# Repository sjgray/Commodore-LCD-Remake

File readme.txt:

CLCD Re-Make Project  by Steve Gray		cbmsteve.ca
====================  and Mike Naberezny        mikenaberezny.com

The goal of this project is to remake/recreate the never released
Commodore LCD computer. Only a few working prototypes were ever
made. These were almost production ready and luckily a few survived
and information about them was released. Thanks go to Jeff Porter
and Bil Herd for helping with this project. Since the LCD computer
was never produced there are no spare parts and no way to replace
them. Several things are no longer available, such as the custom
chips, keyboard, case and LCD Panel, so we must recreate them or
adapt the design to use modern replacements and similar available parts.

Please see the webpage for more info: http://www.cbmsteve.ca/clcd/index.html

*** This is a work in progress!!! The project is currently incomplete.
    Files are provided for information only. Do not attempt to build
    it unless you are willing to debug and fix things. I will not be
    able to support you. As this is a personal project I can not say
    if or when this might be fully functional!

*** GERBER files have not been provided. They may be made available when
    the project is in a more stable/working state.

DESIGN
======

Schematics
----------

Bil Herd had saved all 4 original pages of the CLCD schematics however
one was misplaced. The 3 pages were sent to Mike, scanned in high-res,
and returned to Bil. Later Bil eventually found the missing page and took
several photos. I (Steve) stitched them together into one photo and used
it as a guide for recreating the missing page.

Design Changes
--------------

Since the custom chips and other parts of the computer were not available
I decided to use a CPLD for the MMU/glue and the C128's VDC chip for the
video. A 32K Dual-port RAM was used for the main memory. Both the CPU and
VDC can access this memory independently/simultaneously and the CPU can
write to it directly without the need to go through the VDC registers. This
means writing to the (text) screen works like the original machine. Only
a small patch is needed for the KERNAL.

Western Design Center still makes 6502-series chips and these were used in
the new design. The original 65C102 CPU was replaced with a 65C02 which is
fully compatible. Similarly equivalent WDC IO chips were also available but
in a smaller PLCC package.

Everything is powered by a simple 12V supply.

LCD Panel/Video
---------------

The original 80x16 (480x128 pixel) monochrome LCD panel was replaced by a
modern widescreen colour panel of roughly the same size. It includes a
controller board with HDMI and composite video inputs. We will use the HDMI
input for best quality. The VDC's RGBI output will be converted to HDMI
using an RGB2HDMI converter. There is an RGBI output connector for an
external display.

Keyboard
--------

Two keyboards were designed with MX switches. One design is like the
original keyboard and uses the diamond arrow cursor. The other design uses
an inverted-T cursor. This design was chosen so that normal keycaps
could be used. Included are files to create custom printed keycaps from
maxkeyboard.com. Custom 3D printed keycaps that match the original, including
the diamond cursor, are in progress for the next revision.

EPROM-PLA
---------

The V1 board initially required the EPROM-PLA board, which plugged into the
expansion connector. This board used an EPROM to emulate a PLA that did
decoding for basic functionality. It is no longer required as it has been
replaced by Mike's CPLD implementation.

Case
----

I have designed a case that can be 3D printed. I used Light-beige PLA.
It must be assembled from multiple pieces and requires brass screw inserts
to hold it together. The initial case is an approximation and has been
designed to accommodate the new LCD panel and it's controller and the
RGB2HDMI adapter. All ports are on the back.

Missing Features
----------------

The battery/power, modem, and barcode port features were not implemented in
the initial design but can hopefully be added later as the design progresses.

V1 PROTO
========

V1 is the first prototype that was developed and demonstrated to Jeff Porter
and Bil Herd.

The first prototype PCB was produced but it requires multiple fixes to
correct errors. These were done by Mike. Mike also did further disassembly of
the CLCD KERNAL to be able to re-assemble it back to an original binary and
then patch it to get the VDC working. He also added serial IO for debug purposes.
Mike wrote the CPLD code that functions like a programmed logic array (PLA) to
map in the 32K RAM, KERNAL ROM and IO. The machine is able to boot.

The MMU has not been implemented yet, so the machine can only boot to the
machine-language monitor at this time. The first prototype PCB was a
proof-of-concept and the ports and placement were not designed to match
the original PCB.

I designed a 3D printed case based on existing prototype photos and some original
documentation, but without any complete measurements. It is split into multiple
pieces for easier printing. It is able to open like the original and uses the
inverted-T keyboard version, colour LCD panel with controller and RGB2HDMI adapter.
All ports are along the back of the computer, and the battery compartment allows
access to the RGB2HDMI adapter's buttons.

When Mike visited Jeff he was able to take detailed photographs and measurements
which will be used for the next version. 

V2 PROTO
========

A V2 design is in the works to correct the errors in the V1 Proto PCB.
Additional work is required for the CPLD to add the MMU functionality that
will allow the machine to run the application ROMS, including the normal
menu system.

As of the initial GitHub commit some fixes have been made but there is more
to do. Routing and parts placement is not complete.

A better keyboard will be designed that will support the low-profile MX
switches and use the replica 3D-designed keycaps.

Future Goals
------------

These are just ideas for future goals.

- Better PCB layout to more match the original pcb
- Better keyboard - Low Profile switches and replica keycaps
- Better case
- MMU support for ROM banking and menu system
- Smaller RGBI to HDMI adapter (current is very tight fit)
- Support for graphics mode.
- Modem support? Perhaps a WIFI solution?
- Internal IEC drive?
- Battery power
- Recreation of custom chips.. not easy
- Disassembly of other built-in apps
- Add support for colour or more screen sizes (40x25, 80x25 etc)
- Replica disk drive (1581 case) and printer (Epson P-80)

Additional Info
---------------

My Facebook group............: https://www.facebook.com/groups/806261867281489
Mike's firmware disassembly..: https://github.com/mnaberez/clcd
Mike's firmware and info page: https://mikenaberezny.com/2008/10/04/commodore-lcd-firmware/
Jeff Porter's LCD prototype..: https://flickr.com/photos/mnaberez/albums/72177720308500331/
Jeff Porter's LCD printer....: https://flickr.com/photos/mnaberez/albums/72177720308512645/
Commodore LCD Emulator Online: http://commodore-lcd.lgb.hu/emulator.html
MAME (Has CLCD emulation)....: https://www.mamedev.org/

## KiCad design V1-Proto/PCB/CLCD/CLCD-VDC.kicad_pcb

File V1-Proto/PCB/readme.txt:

CLCD Re-Make Project by Steve Gray and Mike Naberezny
==================== CBMSTEVE.CA

This folder contains:

CLCD      - Kicad design files for CLCD Proto V1 which does not work without fixes
KEYBOARD  - Kicad design files for CLCD Keyboard with Inverted-T cursor. Requires one fix
PLA-BOARD - Kicad design files for EPROM PLA Board - no longer required
_FIXES    - Pictures of fixes required to make the V1 Prototype CLCD board functional

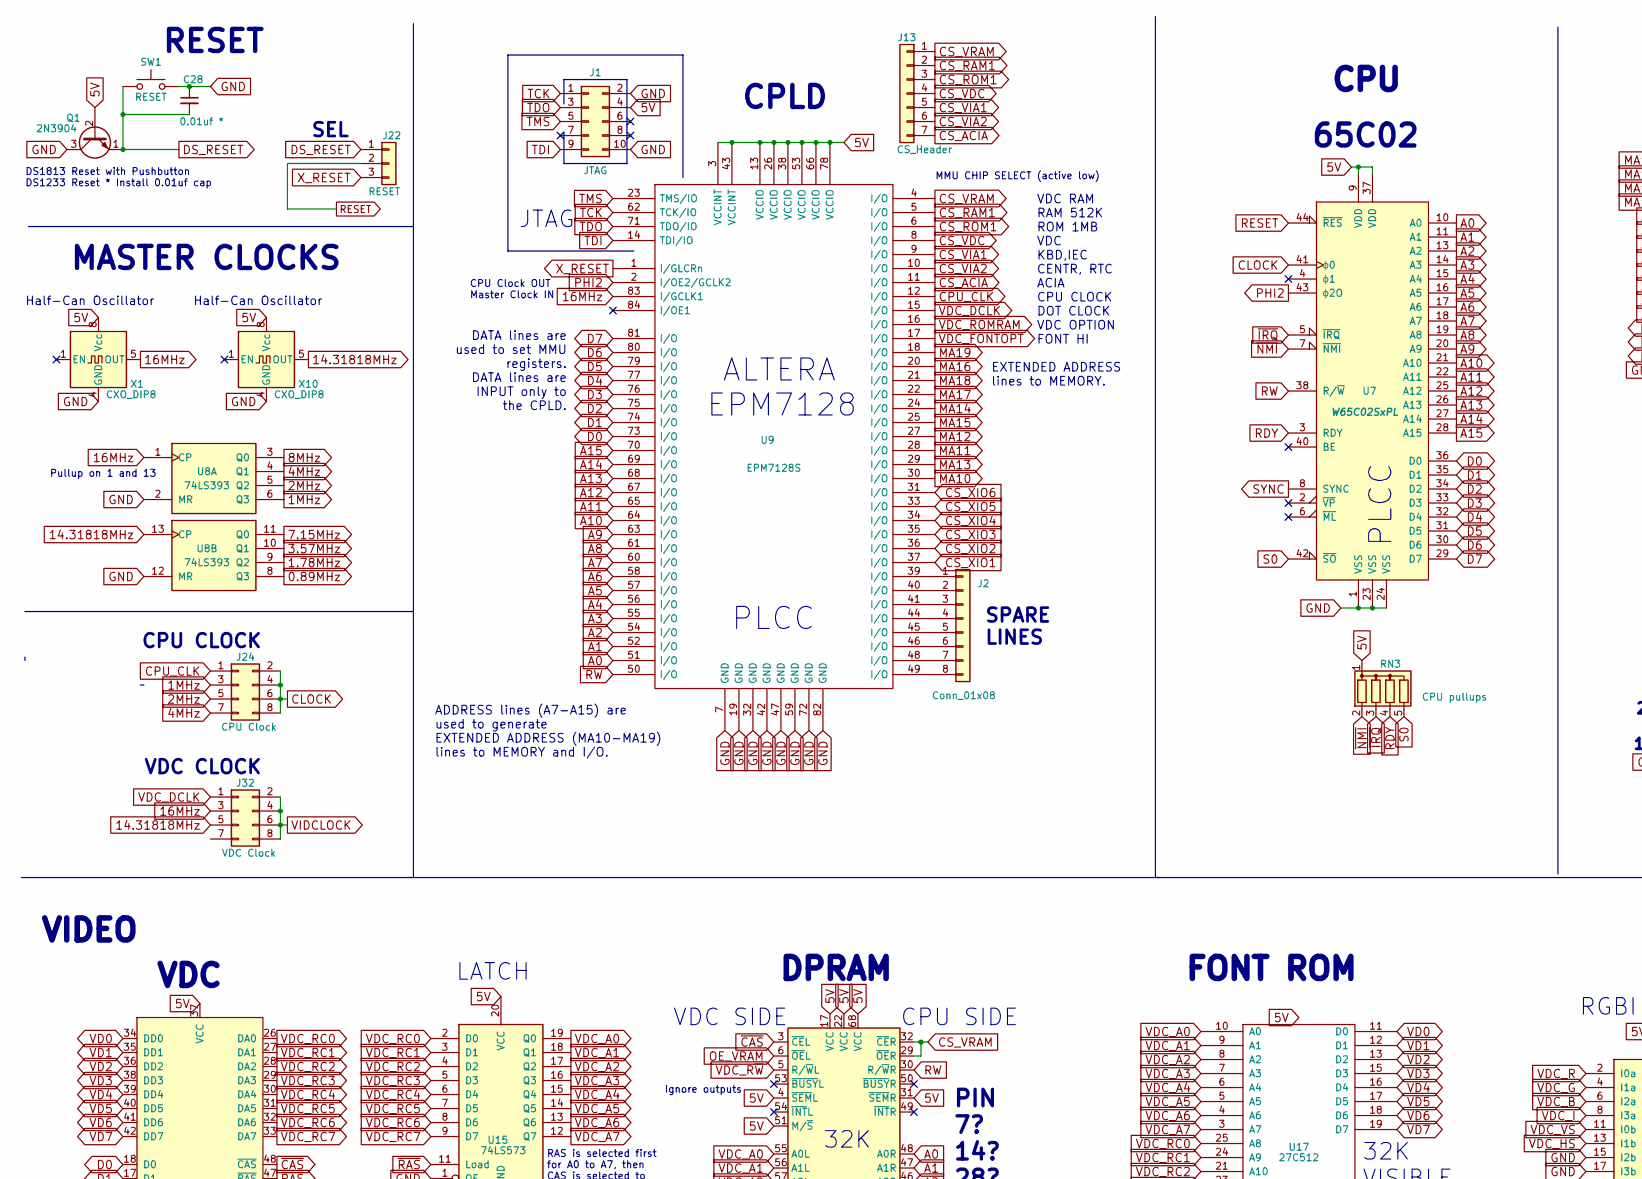
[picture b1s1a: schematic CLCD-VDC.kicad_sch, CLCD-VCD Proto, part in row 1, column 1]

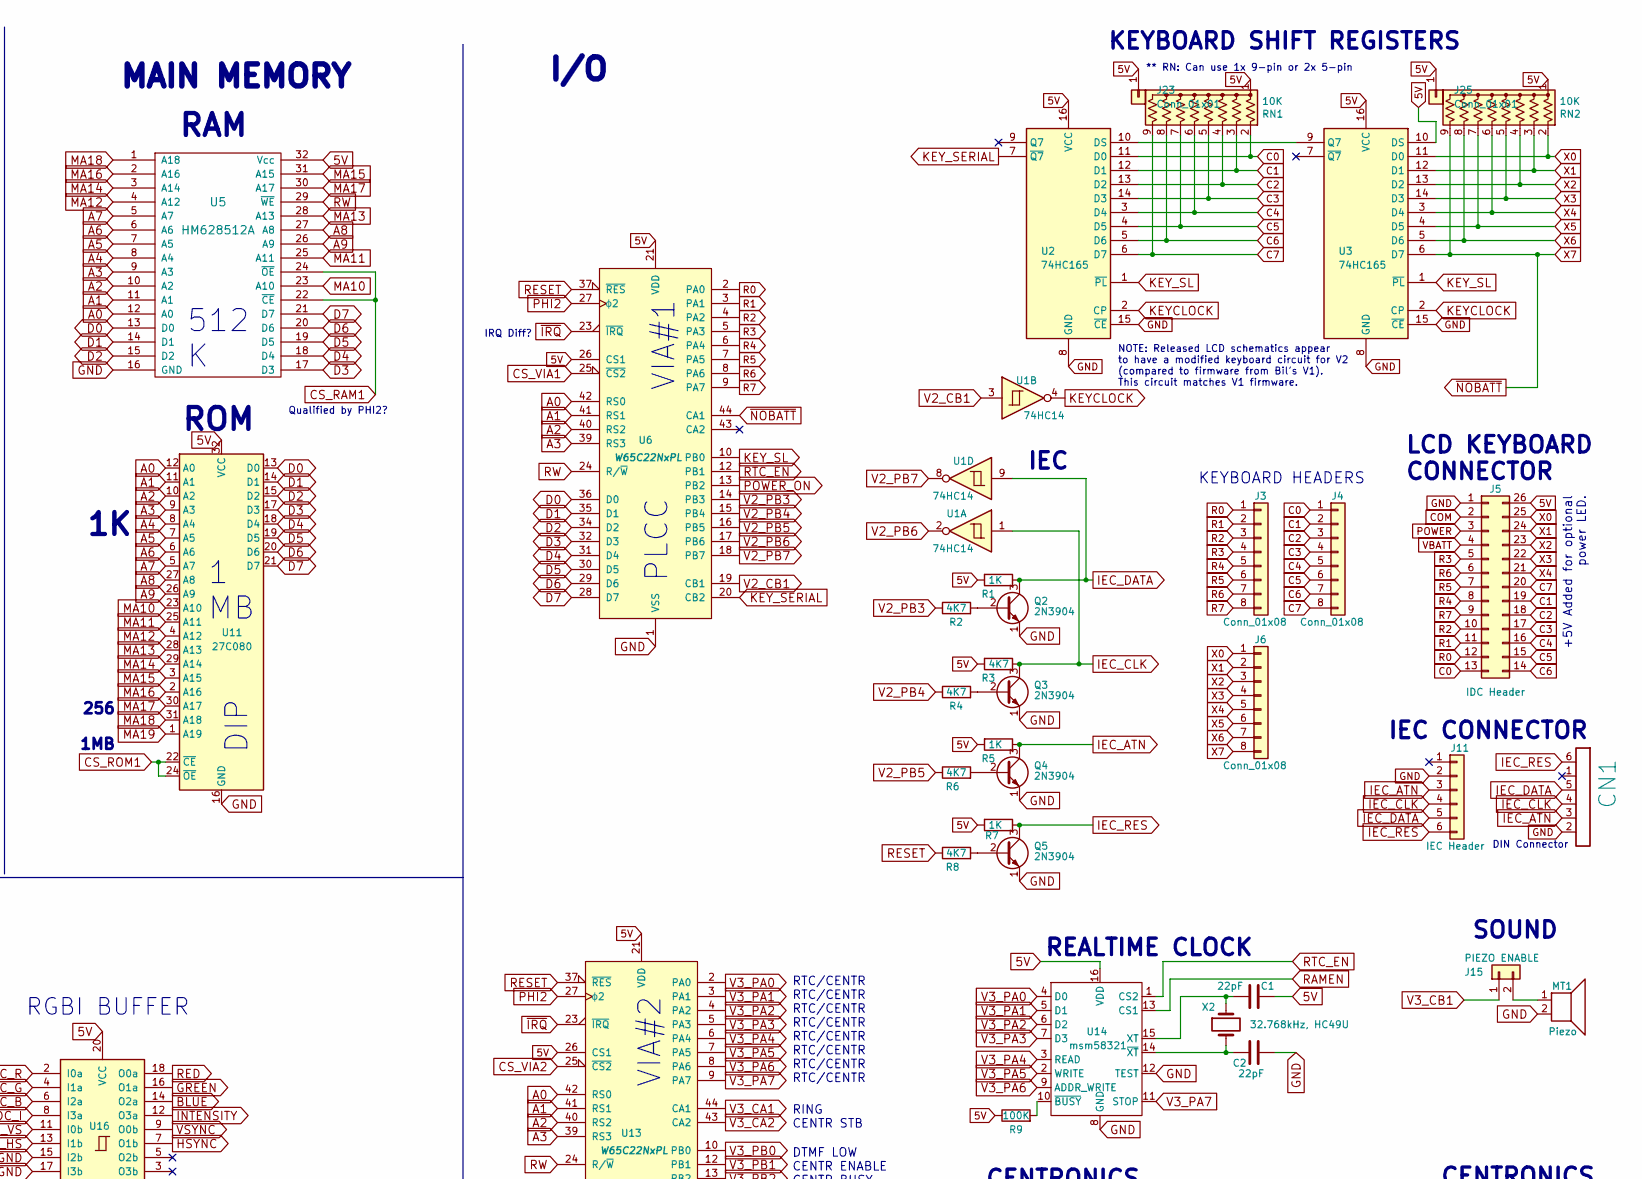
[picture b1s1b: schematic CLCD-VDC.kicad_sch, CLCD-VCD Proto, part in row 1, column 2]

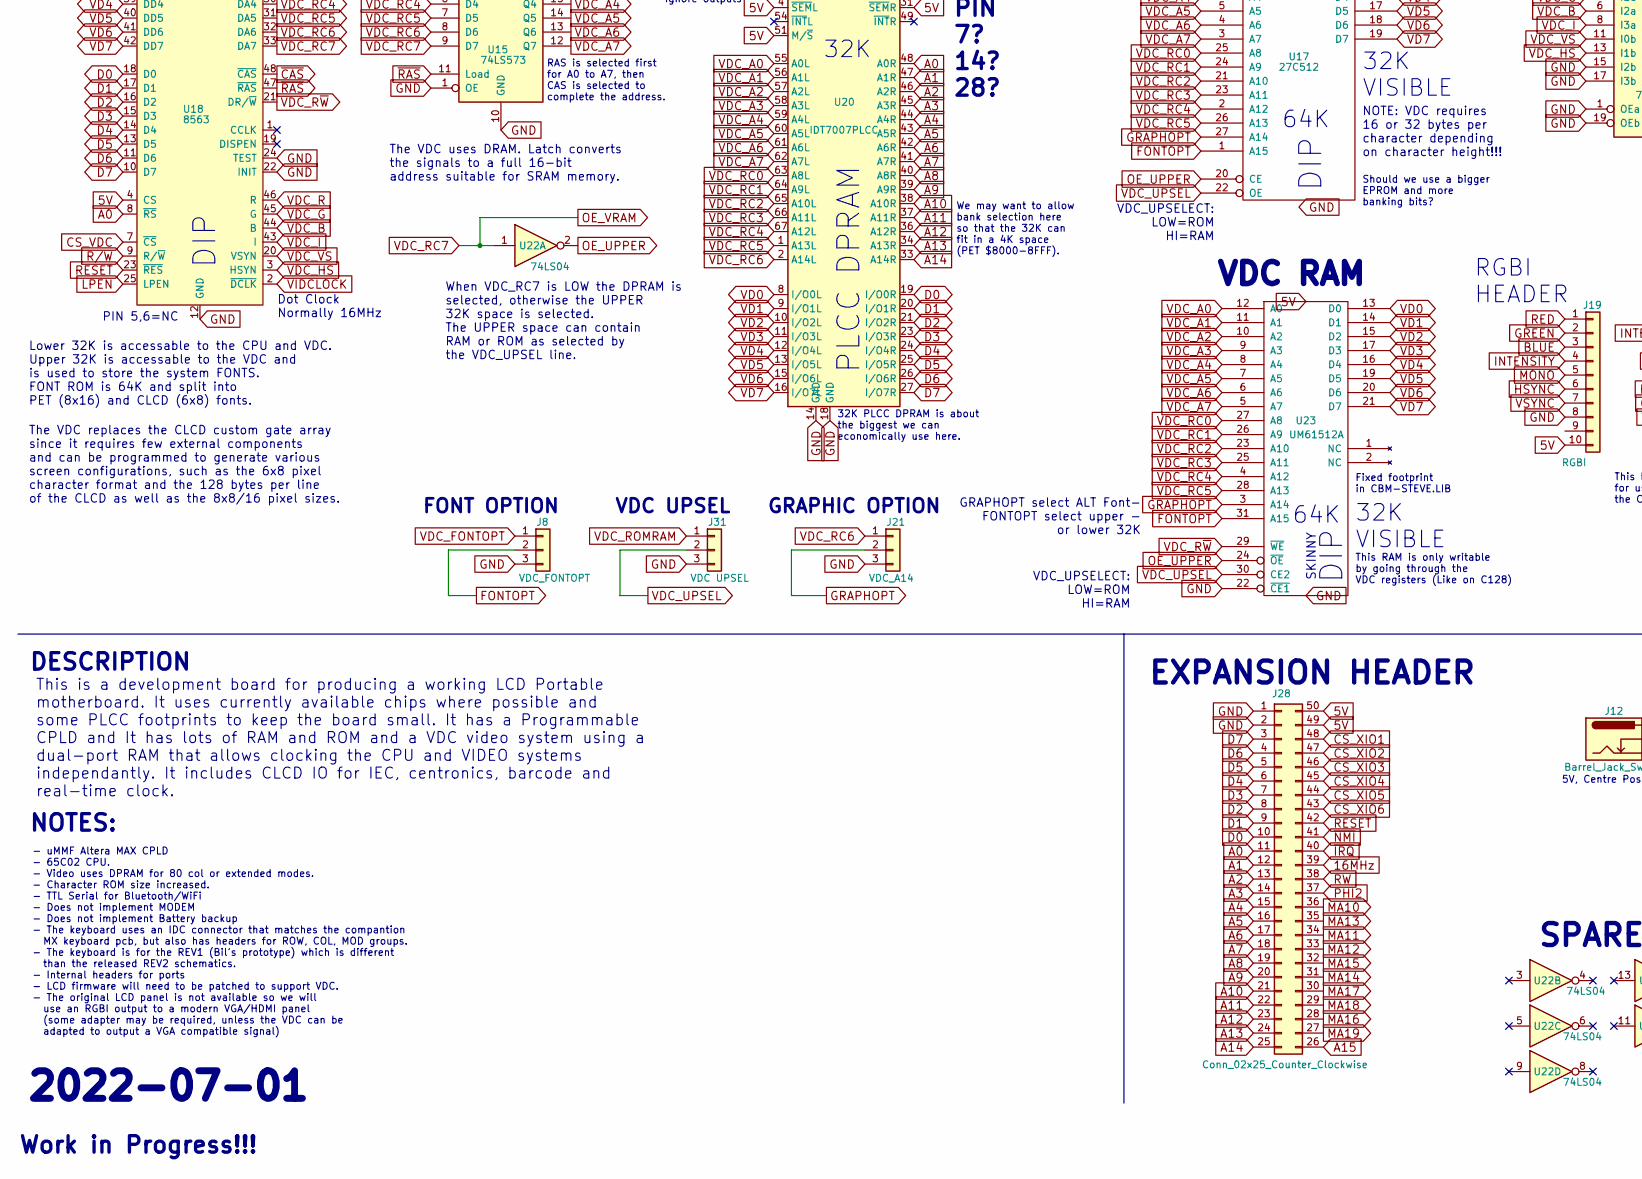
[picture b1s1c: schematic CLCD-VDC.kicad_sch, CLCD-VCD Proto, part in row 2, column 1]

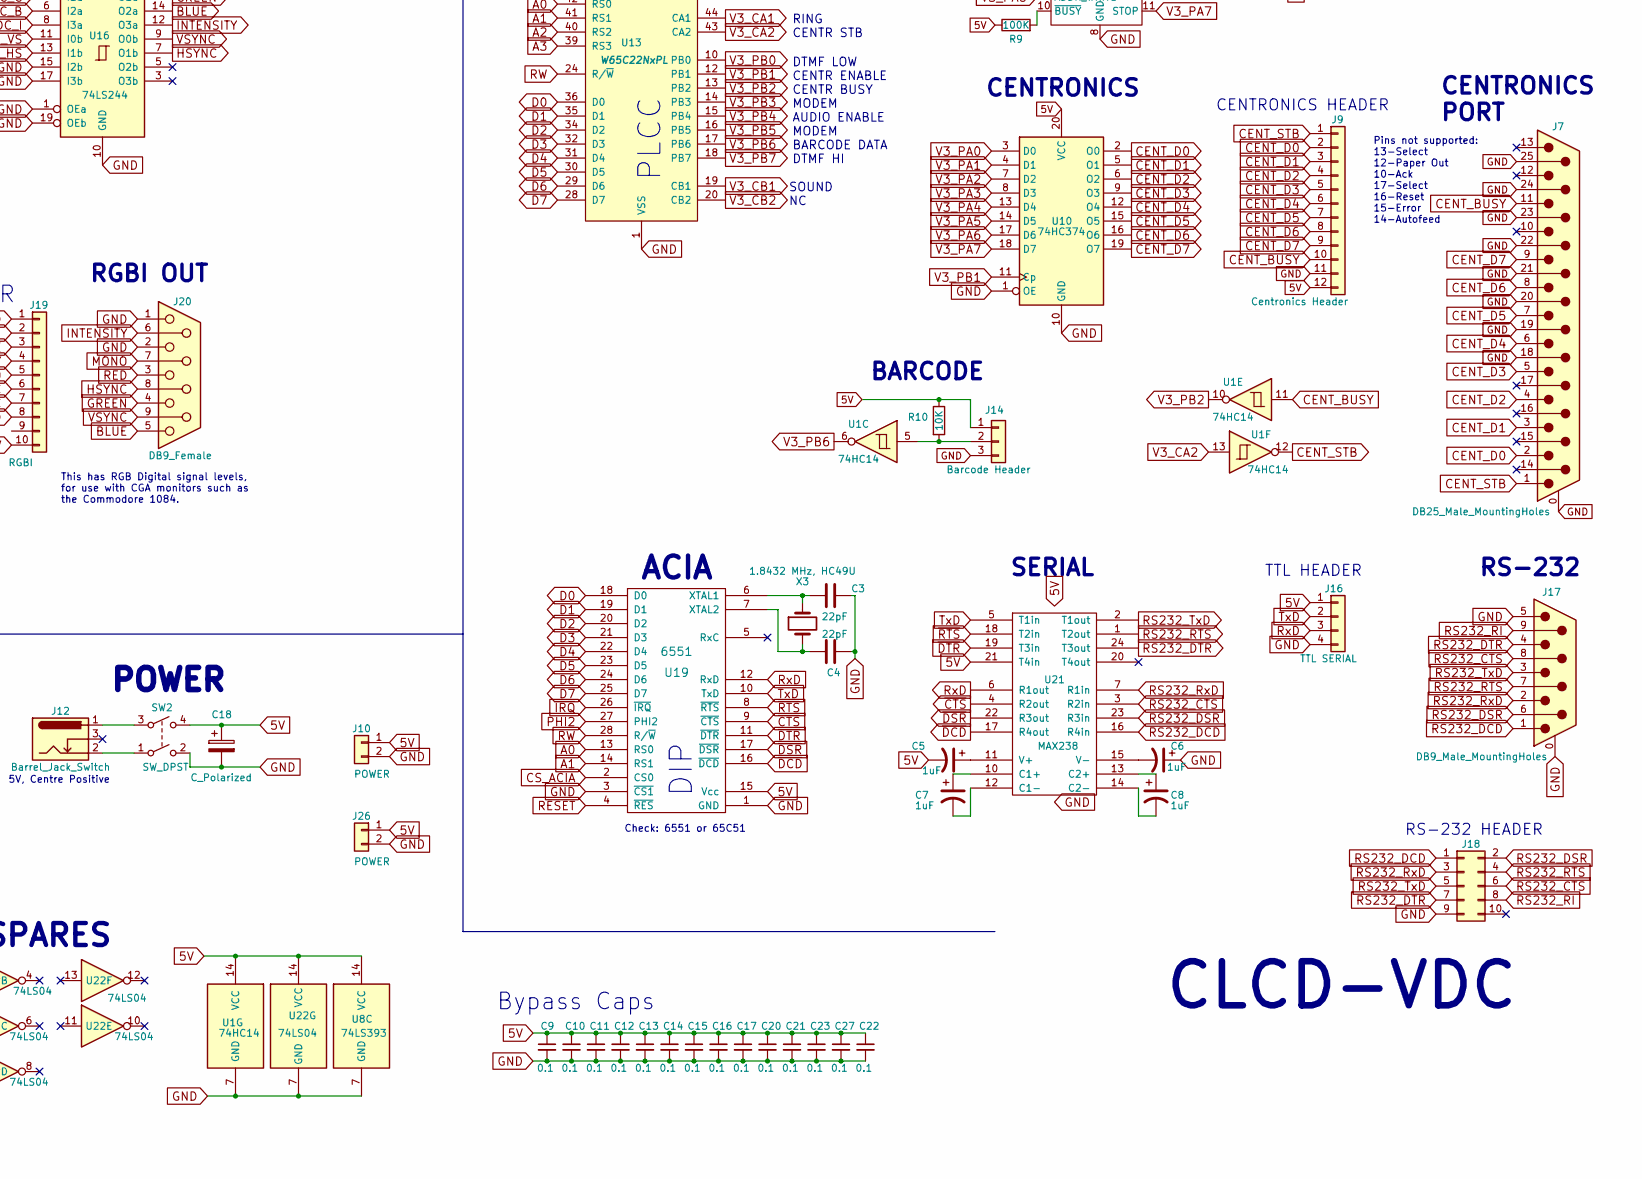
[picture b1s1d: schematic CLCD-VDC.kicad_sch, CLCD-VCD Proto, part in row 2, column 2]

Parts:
C1, C2, C3, C4: 22pF; C_Disc_D4.7mm_W2.5mm_P5.00mm
C5, C6, C7, C8: 1uF; C_Disc_D4.7mm_W2.5mm_P5.00mm
C9, C10, C11, C12, C13, C14, C15, C16, C17, C20, C21, C22, C23, C27: 0.1; C_Disc_D4.7mm_W2.5mm_P5.00mm
C18: C_Polarized; CP_Radial_D7.5mm_P2.50mm
C28: 0.01uf *; C_Disc_D4.7mm_W2.5mm_P5.00mm
CN1: SERIAL_BUS_CON; SERIAL_CON_DIN6
J1: JTAG; PinHeader_2x05_P2.54mm_Vertical
J2, J3, J4, J6: Conn_01x08; PinHeader_1x08_P2.54mm_Vertical
J5: IDC Header; PinHeader_2x13_P2.54mm_Vertical
J7: DB25_Male_MountingHoles; DSUB-25_Male_Horizontal_P2.77x2.84mm_EdgePinOffset4.94mm_Ho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
J8: VDC_FONTOPT; PinHeader_1x03_P2.54mm_Vertical
J9: Centronics Header; PinHeader_1x12_P2.54mm_Vertical
J10, J26: POWER; PinHeader_1x02_P2.54mm_Vertical
J11: IEC Header; PinHeader_1x06_P2.54mm_Vertical
J12: Barrel_Jack_Switch; BarrelJack_Horizontal
J13: CS_Header; PinHeader_1x07_P2.54mm_Vertical
J14: Barcode Header; PinHeader_1x03_P2.54mm_Vertical
J15: PIEZO ENABLE; PinHeader_1x02_P2.54mm_Vertical
J16: TTL SERIAL; PinHeader_1x04_P2.54mm_Vertical
J17: DB9_Male_MountingHoles; DSUB-9_Male_Horizontal_P2.77x2.84mm_EdgePinOffset4.94mm_Hou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
J18: RS232 Header; PinHeader_2x05_P2.54mm_Vertical
J19: RGBI; PinHeader_1x10_P2.54mm_Vertical
J20: DB9_Female; DSUB-9_Female_Horizontal_P2.77x2.84mm_EdgePinOffset4.94mm_H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
J21: VDC_A14; PinHeader_1x03_P2.54mm_Vertical
J22: RESET; PinHeader_1x03_P2.54mm_Vertical
J23, J25: Conn_01x01; PinHeader_1x01_P2.54mm_Vertical
J24: CPU Clock; PinHeader_2x04_P2.54mm_Vertical
J28: Conn_02x25_Counter_Clockwise; PinHeader_2x25_P2.54mm_Vertical
J31: VDC UPSEL; PinHeader_1x03_P2.54mm_Vertical
J32: VDC Clock; PinHeader_2x04_P2.54mm_Vertical
MT1: Piezo; TestPoint_2Pads_Pitch2.54mm_Drill0.8mm
Q1, Q2, Q3, Q4, Q5: 2N3904; TO-92_Inline
R1, R5, R7: 1K; R_Axial_DIN0204_L3.6mm_D1.6mm_P7.62mm_Horizontal
R2, R3, R4, R6, R8: 4K7; R_Axial_DIN0204_L3.6mm_D1.6mm_P7.62mm_Horizontal
R9: 100K; R_Axial_DIN0204_L3.6mm_D1.6mm_P7.62mm_Horizontal
R10: 10K; R_Axial_DIN0204_L3.6mm_D1.6mm_P7.62mm_Horizontal
RN1, RN2: 10K; R_Array_SIP9
RN3: CPU pullups; R_Array_SIP5
SW1: RESET; SW_Tactile_SPST_Angled_PTS645Vx58-2LFS
SW2: SW_DPST; SW_Push_2P1T_Toggle_CK_PVA1xxH2xxxxxxV2
U1: 74HC14; DIP-14_W7.62mm_LongPads
U2, U3: 74HC165; DIP-16_W7.62mm_LongPads
U5: HM628512A; DIP-32_W15.24mm_LongPads
U6, U13: W65C22NxPL; PLCC-44_THT-Socket
U7: W65C02SxPL; PLCC-44_THT-Socket
U8: 74LS393; DIP-14_W7.62mm_LongPads
U9: EPM7128S; PLCC-84_THT-Socket
U10: 74HC374; DIP-20_W7.62mm_LongPads
U11: 27C080; DIP-32_W15.24mm_LongPads
U14: msm58321; DIP-16_W7.62mm_LongPads
U15: 74LS573; DIP-20_W7.62mm_LongPads
U16: 74LS244; DIP-20_W7.62mm_LongPads
U17: 27C512; DIP-28_W15.24mm_LongPads
U18: 8563; DIP-48_W15.24mm_LongPads
U19: 6551; DIP-28_W15.24mm_LongPads
U20: IDT7007PLCC; PLCC-68_THT-Socket
U21: MAX238; DIP-24_W7.62mm_LongPads
U22: 74LS04; DIP-14_W7.62mm_LongPads
U23: UM61512A; DIP-32_W7.62mm
X1, X10: CXO_DIP8; Oscillator_DIP-8
X2: 32.768kHz, HC49U; Crystal_HC49-U_Vertical
X3: 1.8432 MHz, HC49U; Crystal_HC49-U_Vertical

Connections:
0.89MHz: U8.8 (Q3)
1.78MHz: U8.9 (Q2)
1MHz: J24.3, U8.6 (Q3)
2MHz: J24.5, U8.5 (Q2)
3.57MHz: U8.10 (Q1)
4MHz: J24.7, U8.4 (Q1)
5V: C1.2, C5.2, C9.1, C10.1, C11.1, C12.1, C13.1, C14.1, C15.1, C16.1, C17.1, C18.1, C20.1, C21.1, C22.1, C23.1, C27.1, J1.4, J5.26, J9.12, J10.1, J14.1, J16.1, J19.10, J23.1, J25.1, J26.1, J28.49, J28.50, Q1.2 (B), R1.2, R3.2, R5.2, R7.2, R9.1, R10.1, RN1.1 (common), RN2.1 (common), RN3.1 (common), SW2.4, U1.14 (VCC), U2.16 (VCC), U3.10 (DS), U3.16 (VCC), U5.32 (Vcc), U6.21 (VDD), U6.26 (CS1), U7.9 (VDD), U7.37 (VDD), U8.14 (VCC), U9.3 (VCCINT), U9.13 (VCCIO), U9.26 (VCCIO), U9.38 (VCCIO), U9.43 (VCCINT), U9.53 (VCCIO), U9.66 (VCCIO), U9.78 (VCCIO), U10.20 (VCC), U11.32 (VCC), U13.21 (VDD), U13.26 (CS1), U14.16 (VDD), U15.20 (VCC), U16.20 (VCC), U17.28 (VCC), U18.4 (CS), U18.37 (VCC), U19.15 (Vcc), U20.4 (~SEML), U20.17 (VCC), U20.22 (VCC), U20.31 (~SEMR), U20.51 (M/~S), U20.68 (VCC), U21.9 (VCC), U21.21 (T4in), U22.14 (VCC), U23.32 (VCC), X1.8 (Vcc), X10.8 (Vcc)
7.15MHz: U8.11 (Q0)
8MHz: U8.3 (Q0)
14.31818MHz: J32.5, U8.13 (CP), X10.5 (OUT)
16MHz: J28.39, J32.3, U8.1 (CP), U9.83 (I/GCLK1), X1.5 (OUT)
A0: J28.11, U5.12 (A0), U6.42 (RS0), U7.10 (A0), U9.51 (I/O), U11.12 (A0), U13.42 (RS0), U18.8 (~RS), U19.13 (RS0), U20.48 (A0R)
A1: J28.12, U5.11 (A1), U6.41 (RS1), U7.11 (A1), U9.52 (I/O), U11.11 (A1), U13.41 (RS1), U19.14 (RS1), U20.47 (A1R)
A2: J28.13, U5.10 (A2), U6.40 (RS2), U7.13 (A2), U9.54 (I/O), U11.10 (A2), U13.40 (RS2), U20.46 (A2R)
A3: J28.14, U5.9 (A3), U6.39 (RS3), U7.14 (A3), U9.55 (I/O), U11.9 (A3), U13.39 (RS3), U20.45 (A3R)
A4: J28.15, U5.8 (A4), U7.15 (A4), U9.56 (I/O), U11.8 (A4), U20.44 (A4R)
A5: J28.16, U5.7 (A5), U7.16 (A5), U9.57 (I/O), U11.7 (A5), U20.43 (A5R)
A6: J28.17, U5.6 (A6), U7.17 (A6), U9.58 (I/O), U11.6 (A6), U20.42 (A6R)
A7: J28.18, U5.5 (A7), U7.18 (A7), U9.60 (I/O), U11.5 (A7), U20.41 (A7R)
A8: J28.19, U5.27 (A8), U7.19 (A8), U9.61 (I/O), U11.27 (A8), U20.40 (A8R)
A9: J28.20, U5.26 (A9), U7.20 (A9), U9.63 (I/O), U11.26 (A9), U20.39 (A9R)
A10: J28.21, U7.21 (A10), U9.64 (I/O), U20.38 (A10R)
A11: J28.22, U7.22 (A11), U9.65 (I/O), U20.37 (A11R)
A12: J28.23, U7.25 (A12), U9.67 (I/O), U20.36 (A12R)
A13: J28.24, U7.26 (A13), U9.68 (I/O), U20.34 (A13R)
A14: J28.25, U7.27 (A14), U9.69 (I/O), U20.33 (A14R)
A15: J28.26, U7.28 (A15), U9.70 (I/O)
BLUE: J19.3, J20.5, U16.14 (O2a)
C0: J4.1, J5.13, RN1.2 (R1), U2.11 (D0)
C1: J4.2, J5.19, RN1.3 (R2), U2.12 (D1)
C2: J4.3, J5.18, RN1.4 (R3), U2.13 (D2)
C3: J4.4, J5.17, RN1.5 (R4), U2.14 (D3)
C4: J4.5, J5.16, RN1.6 (R5), U2.3 (D4)
C5: J4.6, J5.15, RN1.7 (R6), U2.4 (D5)
C6: J4.7, J5.14, RN1.8 (R7), U2.5 (D6)
C7: J4.8, J5.20, RN1.9 (R8), U2.6 (D7)
CENT_BUSY: J7.11, J9.10, U1.11
CENT_D0: J7.2, J9.2, U10.2 (O0)
CENT_D1: J7.3, J9.3, U10.5 (O1)
CENT_D2: J7.4, J9.4, U10.6 (O2)
CENT_D3: J7.5, J9.5, U10.9 (O3)
CENT_D4: J7.6, J9.6, U10.12 (O4)
CENT_D5: J7.7, J9.7, U10.15 (O5)
CENT_D6: J7.8, J9.8, U10.16 (O6)
CENT_D7: J7.9, J9.9, U10.19 (O7)
CENT_STB: J7.1, J9.1, U1.12
CLOCK: J24.2, J24.4, J24.6, J24.8, U7.41 (ϕ0)
COM: J5.2
CPU_CLK: J24.1, U9.12 (I/O)
CS_ACIA: J13.7, U9.11 (I/O), U19.2 (CS0)
CS_RAM1: J13.2, U5.22 (~CE), U5.24 (~OE), U9.5 (I/O)
CS_ROM1: J13.3, U9.6 (I/O), U11.22 (~CE), U11.24 (~OE)
CS_VDC: J13.4, U9.8 (I/O), U18.7 (~CS)
CS_VIA1: J13.5, U6.25 (~CS2), U9.9 (I/O)
CS_VIA2: J13.6, U9.10 (I/O), U13.25 (~CS2)
CS_VRAM: J13.1, U9.4 (I/O), U20.29 (~OER), U20.32 (~CER)
CS_XIO1: J28.48, U9.37 (I/O)
CS_XIO2: J28.47, U9.36 (I/O)
CS_XIO3: J28.46, U9.35 (I/O)
CS_XIO4: J28.45, U9.34 (I/O)
CS_XIO5: J28.44, U9.33 (I/O)
CS_XIO6: J28.43, U9.31 (I/O)
D0: J28.10, U5.13 (D0), U6.36 (D0), U7.36 (D0), U9.73 (I/O), U11.13 (D0), U13.36 (D0), U18.18 (D0), U19.18 (D0), U20.19 (I/O0R)
D1: J28.9, U5.14 (D1), U6.35 (D1), U7.35 (D1), U9.74 (I/O), U11.14 (D1), U13.35 (D1), U18.17 (D1), U19.19 (D1), U20.20 (I/O1R)
D2: J28.8, U5.15 (D2), U6.34 (D2), U7.34 (D2), U9.75 (I/O), U11.15 (D2), U13.34 (D2), U18.16 (D2), U19.20 (D2), U20.21 (I/O2R)
D3: J28.7, U5.17 (D3), U6.32 (D3), U7.33 (D3), U9.76 (I/O), U11.17 (D3), U13.32 (D3), U18.15 (D3), U19.21 (D3), U20.23 (I/O3R)
D4: J28.6, U5.18 (D4), U6.31 (D4), U7.32 (D4), U9.77 (I/O), U11.18 (D4), U13.31 (D4), U18.14 (D4), U19.22 (D4), U20.24 (I/O4R)
D5: J28.5, U5.19 (D5), U6.30 (D5), U7.31 (D5), U9.79 (I/O), U11.19 (D5), U13.30 (D5), U18.13 (D5), U19.23 (D5), U20.25 (I/O5R)
D6: J28.4, U5.20 (D6), U6.29 (D6), U7.30 (D6), U9.80 (I/O), U11.20 (D6), U13.29 (D6), U18.11 (D6), U19.24 (D6), U20.26 (I/O6R)
D7: J28.3, U5.21 (D7), U6.28 (D7), U7.29 (D7), U9.81 (I/O), U11.21 (D7), U13.28 (D7), U18.10 (D7), U19.25 (D7), U20.27 (I/O7R)
DS_RESET: C28.2, J22.1, Q1.1 (E), SW1.1
FONTOPT: J8.2, U17.1 (A15), U23.31 (A15)
GND: C2.2, C3.2, C4.2, C6.1, C9.2, C10.2, C11.2, C12.2, C13.2, C14.2, C15.2, C16.2, C17.2, C18.2, C20.2, C21.2, C22.2, C23.2, C27.2, C28.1, CN1.2, J1.2, J1.10, J5.1, J7.0 (PAD), J7.18, J7.19, J7.20, J7.21, J7.22, J7.23, J7.24, J7.25, J8.3, J9.11, J10.2, J11.2, J14.3, J16.4, J17.0 (PAD), J17.5, J18.9, J19.8, J20.1, J20.2, J21.3, J26.2, J28.1, J28.2, J31.3, MT1.2, Q1.3 (C), Q2.1 (E), Q3.1 (E), Q4.1 (E), Q5.1 (E), SW1.2, SW2.2, U1.7 (GND), U2.8 (GND), U2.15 (~CE), U3.8 (GND), U3.15 (~CE), U5.16 (GND), U6.1 (VSS), U7.1 (VSS), U7.23 (VSS), U7.24 (VSS), U8.2 (MR), U8.7 (GND), U8.12 (MR), U9.7 (GND), U9.19 (GND), U9.32 (GND), U9.42 (GND), U9.47 (GND), U9.59 (GND), U9.72 (GND), U9.82 (GND), U10.1 (OE), U10.10 (GND), U11.16 (GND), U13.1 (VSS), U14.8 (GND), U14.12 (TEST), U15.1 (OE), U15.10 (GND), U16.1 (OEa), U16.10 (GND), U16.15 (I2b), U16.17 (I3b), U16.19 (OEb), U17.14 (GND), U18.12 (GND), U18.22 (INIT), U18.24 (TEST), U19.1 (GND), U19.3 (~CS1), U20.14 (GND), U20.18 (GND), U21.8 (GND), U22.7 (GND), U23.18 (GND), U23.22 (~CE1), X1.4 (GND), X10.4 (GND)
GRAPHOPT: J21.2, U17.27 (A14), U23.3 (A14)
GREEN: J19.2, J20.4, U16.16 (O1a)
HSYNC: J19.6, J20.8, U16.7 (O1b)
IEC_ATN: CN1.3, J11.3, Q4.3 (C), R5.1
IEC_CLK: CN1.4, J11.4, Q3.3 (C), R3.1, U1.1
IEC_DATA: CN1.5, J11.5, Q2.3 (C), R1.1, U1.9
IEC_RES: CN1.6, J11.6, Q5.3 (C), R7.1
INTENSITY: J19.4, J20.6, U16.12 (O3a)
KEYCLOCK: U1.4, U2.2 (CP), U3.2 (CP)
KEY_SERIAL: U2.7 (~Q7), U6.20 (CB2)
KEY_SL: U2.1 (~PL), U3.1 (~PL), U6.10 (PB0)
LPEN: U18.25 (LPEN)
MA10: J28.36, U5.23 (A10), U9.30 (I/O), U11.23 (A10)
MA11: J28.34, U5.25 (A11), U9.28 (I/O), U11.25 (A11)
MA12: J28.33, U5.4 (A12), U9.27 (I/O), U11.4 (A12)
MA13: J28.35, U5.28 (A13), U9.29 (I/O), U11.28 (A13)
MA14: J28.31, U5.3 (A14), U9.24 (I/O), U11.29 (A14)
MA15: J28.32, U5.31 (A15), U9.25 (I/O), U11.3 (A15)
MA16: J28.28, U5.2 (A16), U9.20 (I/O), U11.2 (A16)
MA17: J28.30, U5.30 (A17), U9.22 (I/O), U11.30 (A17)
MA18: J28.29, U5.1 (A18), U9.21 (I/O), U11.31 (A18)
MA19: J28.27, U9.18 (I/O), U11.1 (A19)
MONO: J19.5, J20.7
unnamed: C1.1, U14.15 (XT), X2.1
unnamed: C2.1, U14.14 (~XT), X2.2
unnamed: C3.1, U19.6 (XTAL1), X3.1
unnamed: C4.1, U19.7 (XTAL2), X3.2
unnamed: C5.1, U21.11 (V+)
unnamed: C6.2, U21.15 (V-)
unnamed: C7.1, U21.10 (C1+)
unnamed: C7.2, U21.12 (C1-)
unnamed: C8.1, U21.13 (C2+)
unnamed: C8.2, U21.14 (C2-)
unnamed: J12.1, SW2.3
unnamed: J12.2, SW2.1
unnamed: J14.2, R10.2, U1.5
unnamed: J15.2, MT1.1
unnamed: Q2.2 (B), R2.2
unnamed: Q3.2 (B), R4.2
unnamed: Q4.2 (B), R6.2
unnamed: Q5.2 (B), R8.2
unnamed: R9.2, U14.10 (~BUSY)
unnamed: U2.10 (DS), U3.9 (Q7)
unnamed: J2.1, U9.39 (I/O)
unnamed: J2.2, U9.40 (I/O)
unnamed: J2.3, U9.41 (I/O)
unnamed: J2.4, U9.44 (I/O)
unnamed: J2.5, U9.45 (I/O)
unnamed: J2.6, U9.46 (I/O)
unnamed: J2.7, U9.48 (I/O)
unnamed: J2.8, U9.49 (I/O)
OE_UPPER: U17.20 (CE), U22.2, U23.24 (~OE)
PHI2: J28.37, U6.27 (ϕ2), U7.43 (ϕ2O), U9.2 (I/OE2/GCLK2), U13.27 (ϕ2), U19.27 (PHI2)
POWER: J5.3
POWER_ON: U6.13 (PB2)
R0: J3.1, J5.12, U6.2 (PA0)
R1: J3.2, J5.11, U6.3 (PA1)
R2: J3.3, J5.10, U6.4 (PA2)
R3: J3.4, J5.5, U6.5 (PA3)
R4: J3.5, J5.8, U6.6 (PA4)
R5: J3.6, J5.7, U6.7 (PA5)
R6: J3.7, J5.6, U6.8 (PA6)
R7: J3.8, J5.9, U6.9 (PA7)
RAMEN: U14.13 (CS1)
RDY: RN3.4 (R3), U7.3 (RDY)
RED: J19.1, J20.3, U16.18 (O0a)
RESET: J22.2, J28.42, R8.1, U6.37 (~RES), U7.44 (~RES), U13.37 (~RES), U18.23 (~RES), U19.4 (~RES)
RS232_CTS: J17.8, J18.6, U21.3 (R2in)
RS232_DCD: J17.1, J18.1, U21.16 (R4in)
RS232_DSR: J17.6, J18.2, U21.23 (R3in)
RS232_DTR: J17.4, J18.7, U21.24 (T3out)
RS232_RI: J17.9, J18.8
RS232_RTS: J17.7, J18.4, U21.1 (T2out)
RS232_RxD: J17.2, J18.3, U21.7 (R1in)
RS232_TxD: J17.3, J18.5, U21.2 (T1out)
RTC_EN: U6.12 (PB1), U14.1 (CS2)
RW: J28.38, U5.29 (~WE), U6.24 (R/~W), U7.38 (R/~W), U9.50 (I/O), U13.24 (R/~W), U19.28 (R/~W), U20.30 (R/~WR)
RxD: J16.3, U19.12 (RxD), U21.6 (R1out)
R/W: U18.9 (R/~W)
S0: RN3.5 (R4), U7.42 (~SO)
SYNC: U7.8 (SYNC)
TCK: J1.1, U9.62 (TCK/IO)
TDI: J1.9, U9.14 (TDI/IO)
TDO: J1.3, U9.71 (TDO/IO)
TMS: J1.5, U9.23 (TMS/IO)
TxD: J16.2, U19.10 (TxD), U21.5 (T1in)
V2_CB1: U1.3, U6.19 (CB1)
V2_PB3: R2.1, U6.14 (PB3)
V2_PB4: R4.1, U6.15 (PB4)
V2_PB5: R6.1, U6.16 (PB5)
V2_PB6: U1.2, U6.17 (PB6)
V2_PB7: U1.8, U6.18 (PB7)
V3_CA1: U13.44 (CA1)
V3_CA2: U1.13, U13.43 (CA2)
V3_CB1: J15.1, U13.19 (CB1)
V3_CB2: U13.20 (CB2)
V3_PA0: U10.3 (D0), U13.2 (PA0), U14.4 (D0)
V3_PA1: U10.4 (D1), U13.3 (PA1), U14.5 (D1)
V3_PA2: U10.7 (D2), U13.4 (PA2), U14.6 (D2)
V3_PA3: U10.8 (D3), U13.5 (PA3), U14.7 (D3)
V3_PA4: U10.13 (D4), U13.6 (PA4), U14.3 (READ)
V3_PA5: U10.14 (D5), U13.7 (PA5), U14.2 (WRITE)
V3_PA6: U10.17 (D6), U13.8 (PA6), U14.9 (ADDR_WRITE)
V3_PA7: U10.18 (D7), U13.9 (PA7), U14.11 (STOP)
V3_PB0: U13.10 (PB0)
V3_PB1: U10.11 (Cp), U13.12 (PB1)
V3_PB2: U1.10, U13.13 (PB2)
V3_PB3: U13.14 (PB3)
V3_PB4: U13.15 (PB4)
V3_PB5: U13.16 (PB5)
V3_PB6: U1.6, U13.17 (PB6)
V3_PB7: U13.18 (PB7)
VBATT: J5.4
VD0: U17.11 (D0), U18.34 (DD0), U20.8 (I/O0L), U23.13 (D0)
VD1: U17.12 (D1), U18.35 (DD1), U20.9 (I/O1L), U23.14 (D1)
VD2: U17.13 (D2), U18.36 (DD2), U20.10 (I/O2L), U23.15 (D2)
VD3: U17.15 (D3), U18.38 (DD3), U20.11 (I/O3L), U23.17 (D3)
VD4: U17.16 (D4), U18.39 (DD4), U20.12 (I/O4L), U23.16 (D4)
VD5: U17.17 (D5), U18.40 (DD5), U20.13 (I/O5L), U23.19 (D5)
VD6: U17.18 (D6), U18.41 (DD6), U20.15 (I/O6L), U23.20 (D6)
VD7: U17.19 (D7), U18.42 (DD7), U20.16 (I/O7L), U23.21 (D7)
VDC_A0: U15.19 (Q0), U17.10 (A0), U20.55 (A0L), U23.12 (A0)
VDC_A1: U15.18 (Q1), U17.9 (A1), U20.56 (A1L), U23.11 (A1)
VDC_A2: U15.17 (Q2), U17.8 (A2), U20.57 (A2L), U23.10 (A2)
VDC_A3: U15.16 (Q3), U17.7 (A3), U20.58 (A3L), U23.9 (A3)
VDC_A4: U15.15 (Q4), U17.6 (A4), U20.59 (A4L), U23.8 (A4)
VDC_A5: U15.14 (Q5), U17.5 (A5), U20.60 (A5L), U23.7 (A5)
VDC_A6: U15.13 (Q6), U17.4 (A6), U20.61 (A6L), U23.6 (A6)
VDC_A7: U15.12 (Q7), U17.3 (A7), U20.62 (A7L), U23.5 (A7)
VDC_B: U16.6 (I2a), U18.44 (B)
VDC_DCLK: J32.1, U9.15 (I/O)
VDC_FONTOPT: J8.1, U9.17 (I/O)
VDC_G: U16.4 (I1a), U18.45 (G)
VDC_HS: U16.13 (I1b), U18.3 (HSYN)
VDC_I: U16.8 (I3a), U18.43 (I)
VDC_R: U16.2 (I0a), U18.46 (R)
VDC_RC0: U15.2 (D0), U17.25 (A8), U18.26 (DA0), U20.63 (A8L), U23.27 (A8)
VDC_RC1: U15.3 (D1), U17.24 (A9), U18.27 (DA1), U20.64 (A9L), U23.26 (A9)
VDC_RC2: U15.4 (D2), U17.21 (A10), U18.28 (DA2), U20.65 (A10L), U23.23 (A10)
VDC_RC3: U15.5 (D3), U17.23 (A11), U18.29 (DA3), U20.66 (A11L), U23.25 (A11)
VDC_RC4: U15.6 (D4), U17.2 (A12), U18.30 (DA4), U20.67 (A12L), U23.4 (A12)
VDC_RC5: U15.7 (D5), U17.26 (A13), U18.31 (DA5), U20.1 (A13L), U23.28 (A13)
VDC_RC6: J21.1, U15.8 (D6), U18.32 (DA6), U20.2 (A14L)
VDC_RC7: U15.9 (D7), U18.33 (DA7), U20.6 (~OEL), U22.1
VDC_ROMRAM: J31.1, U9.16 (I/O)
VDC_R~W: U18.21 (DR/~W), U20.5 (R/~WL), U23.29 (~WE)
VDC_UPSEL: J31.2, U17.22 (OE), U23.30 (CE2)
VDC_VS: U16.11 (I0b), U18.20 (VSYN)
VIDCLOCK: J32.2, J32.4, J32.6, J32.8, U18.2 (~DCLK)
VSYNC: J19.7, J20.9, U16.9 (O0b)
X0: J5.25, J6.1, RN2.2 (R1), U3.11 (D0)
X1: J5.24, J6.2, RN2.3 (R2), U3.12 (D1)
X2: J5.23, J6.3, RN2.4 (R3), U3.13 (D2)
X3: J5.22, J6.4, RN2.5 (R4), U3.14 (D3)
X4: J5.21, J6.5, RN2.6 (R5), U3.3 (D4)
X5: J6.6, RN2.7 (R6), U3.4 (D5)
X6: J6.7, RN2.8 (R7), U3.5 (D6)
X7: J6.8, RN2.9 (R8), U3.6 (D7), U6.44 (CA1)
X_RESET: J22.3, U9.1 (I/GLCRn)
~CAS: U18.48 (~CAS), U20.3 (~CEL)
~CTS: U19.9 (~CTS), U21.4 (R2out)
~DCD: U19.16 (~DCD), U21.17 (R4out)
~DSR: U19.17 (~DSR), U21.22 (R3out)
~DTR: U19.11 (~DTR), U21.19 (T3in)
~IRQ: J28.40, RN3.3 (R2), U6.23 (~IRQ), U7.5 (~IRQ), U13.23 (~IRQ), U19.26 (~IRQ)
~NMI: J28.41, RN3.2 (R1), U7.7 (~NMI)
~RAS: U15.11 (Load), U18.47 (~RAS)
~RTS: U19.8 (~RTS), U21.18 (T2in)

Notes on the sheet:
VDC_UPSELECT: LOW=ROM HI=RAM
SEL
DESCRIPTION
RGBI OUT
I/O
RTC/CENTR RTC/CENTR RTC/CENTR RTC/CENTR RTC/CENTR RTC/CENTR RTC/CENTR RTC/CENTR
IEC
ROM
TTL HEADER
PLCC
MAIN MEMORY
RGBI BUFFER
JTAG
CPLD
VIA#1
NOTE: VDC requires 16 or 32 bytes per character depending on character height!!!
Pins not supported: 13-Select 12-Paper Out 10-Ack 17-Select 16-Reset 15-Error 14-Autofeed
VDC RAM
PIN 7? 14? 28?
KEYBOARD HEADERS
CPU SIDE
REALTIME CLOCK
KEYBOARD SHIFT REGISTERS
Work in Progress!!!
MASTER CLOCKS
Dot Clock Normally 16MHz
Should we use a bigger EPROM and more banking bits?
VDC SIDE
Half-Can Oscillator
NOTES:
ACIA
DIP
EXTENDED ADDRESS lines to MEMORY.
FONT ROM
IEC CONNECTOR
EPM7128
This is a development board for producing a working LCD Portable motherboard. It uses currently available chips where possible and some PLCC footprints to keep the board small. It has a Programmable CPLD and It has lots of RAM and ROM and a VDC video system using a dual-port RAM that allows clockin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
DIN Connector
DS1813 Reset with Pushbutton DS1233 Reset * Install 0.01uf cap
64K

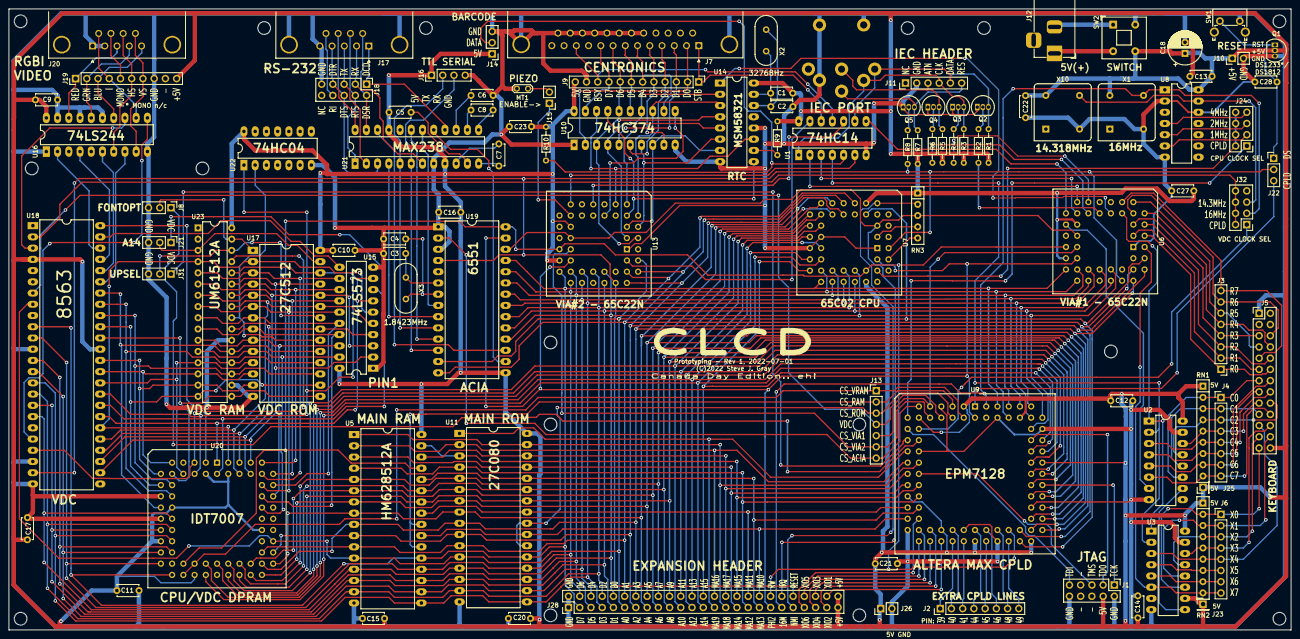
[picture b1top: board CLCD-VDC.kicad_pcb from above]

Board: 2 copper layers, 290.0 x 140.5 mm, 100 parts (0 on the bottom side), 221 nets.

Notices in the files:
V1-Proto/PCB/CLCD/CLCD-VDC.kicad_pcb:
(C)2022 Steve J. Gray
